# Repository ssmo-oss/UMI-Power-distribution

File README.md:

# UMI Power Distribution

Three separate boards distribute a 12 V supply to the UMI system. **D6 is the current prototype revision. It has not been physically qualified or approved for production.**

## Latest mechanical candidate — D8-2L MAIN

The owner supplied [10052938_AA-UMI POWER PCB OUTLINE V3.dxf](design/D8-2L/source/10052938_AA-UMI%20POWER%20PCB%20OUTLINE%20V3.dxf) for MAIN only on 2026-10-01. [D8-2L](design/D8-2L/README.md) and [D8-2L-FASTON](design/D8-2L-FASTON/README.md) apply the updated contour and six 3.5 mm mounting-hole centers. The FASTON assembly was corrected on 2026-10-01: the right-angle tabs now point toward board top, their through-board pins align with the two-hole footprints, and the reverse-side fuseholder envelopes align with their pad patterns. The FASTON board passes DRC with zero violations, unconnected items, and schematic-parity issues. Its [STEP assembly](design/D8-2L-FASTON/MAIN_POWER/MAIN_POWER_D8_FASTON.step) and [3D preview](design/D8-2L-FASTON/MAIN_POWER/review/MAIN_POWER_D8_FASTON_3D.png) are current. The terminal and fuseholder solids are dimension-based simplified CAD envelopes, not exact vendor models; TE lists the 63951-4 as a 6.35 mm-wide right-angle tab with 1.4 mm PCB holes and an 8.89 mm profile height ([TE product page](https://www.te.com/en/product-63951-4.html)). Raw copper is excluded and solder-mask surfaces are included in the STEP. The direct-solder variant was left untouched. TE recommends 1.57 mm PCB thickness, while the candidate remains 1.2 mm pending confirmation. D7-2L remains unchanged.

**D8 is not ready for manufacturing.** KiCad 10.0.6 DRC reports 0 violations, 0 unconnected items, and 0 schematic-parity issues for both MAIN variants. Complete electrical, thermal, and enclosure review before release. See the saved [D8 DRC report](design/D8-2L/MAIN_POWER/verification/D8_DRC_DIRECT_SOLDER.json), [board preview](design/D8-2L/MAIN_POWER/review/MAIN_POWER_D8.svg), and [visual STEP assembly](design/D8-2L/MAIN_POWER/MAIN_POWER_D8.step). The direct-solder STEP includes the board and all 10 component envelopes. The FASTON variant includes the board and all 11 component envelopes. Input leads and mating cables are omitted.

| Board | Function | PCB size / thickness | Planned assembly |
|---|---|---|---|
| MAIN_POWER | Fused 12 V distribution | 68 Ãƒâ€” 100.264 mm / 1.2 mm | User fits all 11 through-hole parts |
| POE_POWER | 12 V to nominal 53.5 V, 1.31 A switch supply | 106 Ãƒâ€” 100 mm / 1.2 mm | JLC SMT, user fits 3 through-hole parts |
| USB_POWER | Two charge-only USB-A ports, 3 A electrical design target each | 80 Ãƒâ€” 50 mm / 1.6 mm | JLC SMT, user fits 3 through-hole parts |

All boards use four copper layers, 2 oz outer / 1 oz inner. Planned batch: **10 of each board**. Enclosure ambient limit: **40 Ã‚Â°C**.

## Mechanical update required

On 2026-09-28, the project owner confirmed that the D6 board outlines were out of date. D8-2L now applies the supplied replacement outline to MAIN only. D6 manufacturing files and STEP models remain historical and on hold; POE and USB replacement mechanics are still not supplied. Do not treat D8 as released for manufacture.

## Latest MAIN option: D7-2L

[Two-layer MAIN prototype](design/D7-2L/README.md) preserves the user layout and uses 2 oz copper on each side at 1.2 mm thickness. Native ERC/DRC/parity checks pass. The four-layer D6L1 option remains preserved. Full shared-path voltage-drop/thermal qualification and mechanical confirmation remain pending. PoE and USB are unchanged. [Download D7-2L](packages/UMI_MAIN_POWER_D7_2L_PROTOTYPE.zip).

## Preserved four-layer MAIN layout: D6L1

The user rearranged MAIN components on 2026-09-29. [D6L1](design/D6L1/README.md) restores the branch connections and fills while preserving those placements and graphics. Native DRC/parity: zero violations and zero unconnected items. [Open the current MAIN project](design/D6L1/MAIN_POWER/MAIN_POWER.kicad_pro). Older MAIN Gerbers and STEP files are now stale for this layout. Manufacturing remains on hold.

## MAIN schematic redraw: D6S1

The MAIN schematic was redrawn on 2026-09-29 with explicit branch wiring. [Open the D6S1 project](design/D6S1/MAIN_POWER/MAIN_POWER.kicad_pro), [view the schematic PDF](design/D6S1/MAIN_POWER/review/MAIN_POWER_schematic.pdf), or read the [revision notes](design/D6S1/README.md). The physical MAIN PCB is unchanged from D6; PoE and USB remain D6. The outline hold still applies. For another computer or agent, read [START_HERE.md](START_HERE.md).

## Start here

- [D6 design and manufacturing overview](design/D6/README.md)
- KiCad 10 projects: [MAIN](design/D6/MAIN_POWER/MAIN_POWER.kicad_pro), [POE](design/D6/POE_POWER/POE_POWER.kicad_pro), [USB](design/D6/USB_POWER/USB_POWER.kicad_pro). Each project includes its PCB, schematic and local libraries.
- [Complete D6 prototype package](packages/UMI_THREE_BOARD_DESIGN_D6_PROTOTYPE.zip)
- [Combined component sourcing spreadsheet](design/D6/UMI_COMPONENT_SOURCING.xlsx) and [CSV](design/D6/UMI_COMPONENT_SOURCING.csv): one list for SMT, manual parts and harness parts.
- [Layout review](design/D6/LAYOUT_REVIEW.html): download/clone and open locally to view linked fabrication and assembly drawings.
- [Simplified STEP models](mechanical/D6/README.md) and [STEP ZIP](packages/UMI_D6_STEP.zip).
- [Engineering calculations and bring-up procedure](design/D6/ENGINEERING_AND_TEST_NOTES.md), [fabrication requirements](design/D6/FABRICATION_NOTES.md), [manual assembly](design/D6/MANUAL_ASSEMBLY.md).
- [Open items and project decisions](docs/PROJECT_HANDOFF.md).

## Configuration

The PoE switch and SENSING GMSL board are **alternative configurations; never connect both loads** under this power budget. No hardware interlock enforces this. The larger configuration is approximately 174 W / 14.5 A at 12 V under the documented assumptions; retain the 20 A input-path design/test margin.

MAIN J1 is the 12 V input. MAIN J2/J3/J4/J5/J6 feed Jetson/GMSL/fan/USB/POE respectively. All two-pin 12 V headers use pin 1 positive, pin 2 ground. POE J6 supplies 53.5 V: pin 1 positive, pin 2 unused, pin 3 ground. Consult the project pin schedules before making cables.

## Verification and limitations

The supplied D6 records report zero KiCad DRC/ERC violations, zero unconnected items and zero schematic-parity issues. Gerber/drill/placement checks and source hashes are included in each board's verification folder. These are file checks, not hardware measurements. [TEST_RECORD.csv](design/D6/TEST_RECORD.csv) records physical tests as unperformed.

Supplier acceptance of copper thickness, selective filled/capped vias and the PoE inductor fixture is pending. Stock observations are historical snapshots, not reservations. The output fuse is obsolete and its observed stock only supports a batch sourcing plan. No order or payment has been placed.

STEP files preserve board outlines and holes and add simplified component proxies. Component heights are estimates: do not use them for final enclosure-clearance signoff. Missing KiCad 3D bodies do not remove a component from the assembly BOM; check the SMT BOM/CPL and separately fitted parts.

## Repository contents

`design/D6/` is the editable current design and manufacturing package. `mechanical/D6/` contains six STEP models and their verification/assumptions. `packages/` contains the original current delivery ZIPs. `archive/` contains superseded snapshots, including the original revC input. `docs/historical-reviews/` preserves prior engineering reviews; they can contain findings later resolved by D6. `tools/legacy/` contains development scripts, with execution caveats in its README.

Transferred on 2026-09-28. See [transfer record](docs/TRANSFER_RECORD.md) and [SHA256 manifest](TRANSFER_SHA256SUMS.txt). No license has been selected; this import does not assign new licensing terms to project files or third-party library assets.

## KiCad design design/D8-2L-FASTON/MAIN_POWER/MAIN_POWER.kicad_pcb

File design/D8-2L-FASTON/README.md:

# D8 MAIN — FASTON 250 input alternative

This separate MAIN-board variant is based on D8-2L. It uses the owner-supplied V3 outline and keeps the fuse and connector arrangement, routing, copper zones, and output connectors. J1 is changed to two TE Connectivity 63951-4 FASTON 250 PCB tabs, each with two plated mounting holes (four holes total) on the tab axis, with both blade axes pointing toward the board's top edge in the top view. The flat solder-pad version remains in `design/D8-2L/MAIN_POWER/`.

The FASTON pair is centered on the board's 139.6 mm X centerline. Its footprint courtyard sits 2.5 mm in from the straight lower board edge.

## Input connector

- PCB terminals: TE Connectivity **63951-4**, quantity 2; FASTON 250, 6.35 × 0.8 mm tabs. Each tab uses two 1.4 mm plated holes at 5.08 mm pitch.
- Mating 10 AWG receptacle option: TE Connectivity **62998-2**, quantity 2, for 10–8 AWG wire. The mating receptacles and wires are off-board, not fitted to the PCB.
- TE lists 8.89 mm profile height from PCB for 63951-4, leaving 1.11 mm nominal margin under 10 mm. The same product page recommends 1.57 mm board thickness. This variant still uses 1.2 mm board thickness; confirm fit/retention with TE or update the stackup before ordering.
- The 10 mm clearance also needs checking with the selected female receptacles and wires installed. The TE 63951-4 summary does not state a current rating, so qualify the complete connection thermally at the intended maximum current. Terminals have no wire-insulation support; add harness strain relief.

## Files

- `MAIN_POWER/MAIN_POWER.kicad_pcb` — updated PCB; copper zones refilled.
- `MAIN_POWER/MAIN_POWER.kicad_sch` — J1 value, footprint, MPN and BOM status updated.
- `MAIN_POWER/UMI_D2.pretty/Input_FASTON_250_PAIR.kicad_mod` — pair footprint with four 1.4 mm plated holes (two per tab, 5.08 mm pitch) and top-view tab orientation shown on F.Fab.
- `MAIN_POWER/verification/D8_FASTON_DRC.json` — KiCad 10.0.6 check after V3 outline and zone refill: 0 rule violations, 0 unconnected items, and 0 schematic-parity warnings. The six DXF-derived 3.5 mm mounting holes have matching schematic records.
- `MAIN_POWER/review/MAIN_POWER_D8_FASTON.svg` — top-view preview.
- `MAIN_POWER/MAIN_POWER_D8_FASTON.step` — refreshed 2026-10-01; board, solder-mask surfaces, and all 11 modeled components (J1–J6 and F1–F5); raw tracks, pads, and zones are excluded.
- `MAIN_POWER/review/MAIN_POWER_D8_FASTON_3D.png` — 3D assembly preview showing the input blades extending toward the board top and the fuse-holder envelopes aligned over their backside pad patterns.

The STEP uses dimensioned envelope models for the TE 63951-4 terminal pair, the JST VH output headers, and the Littelfuse FLR fuse holders. They are simplified solid envelopes, not detailed vendor CAD. The FASTON pair uses a 6.35 × 0.8 mm blade, 8.89 mm profile height, four tails aligned to the four 1.4 mm holes, and a right-angle bend; the two blades point toward the board top, parallel to the fuse row. The B.Cu fuseholder envelopes are mirrored to match the pad patterns. TE recommends a 1.57 mm board; this candidate is still 1.2 mm. Confirm the terminal fit, 10 mm enclosure clearance, current capacity, and mating connector with exact vendor CAD before release. This remains a prototype layout candidate, not a manufacturing release.

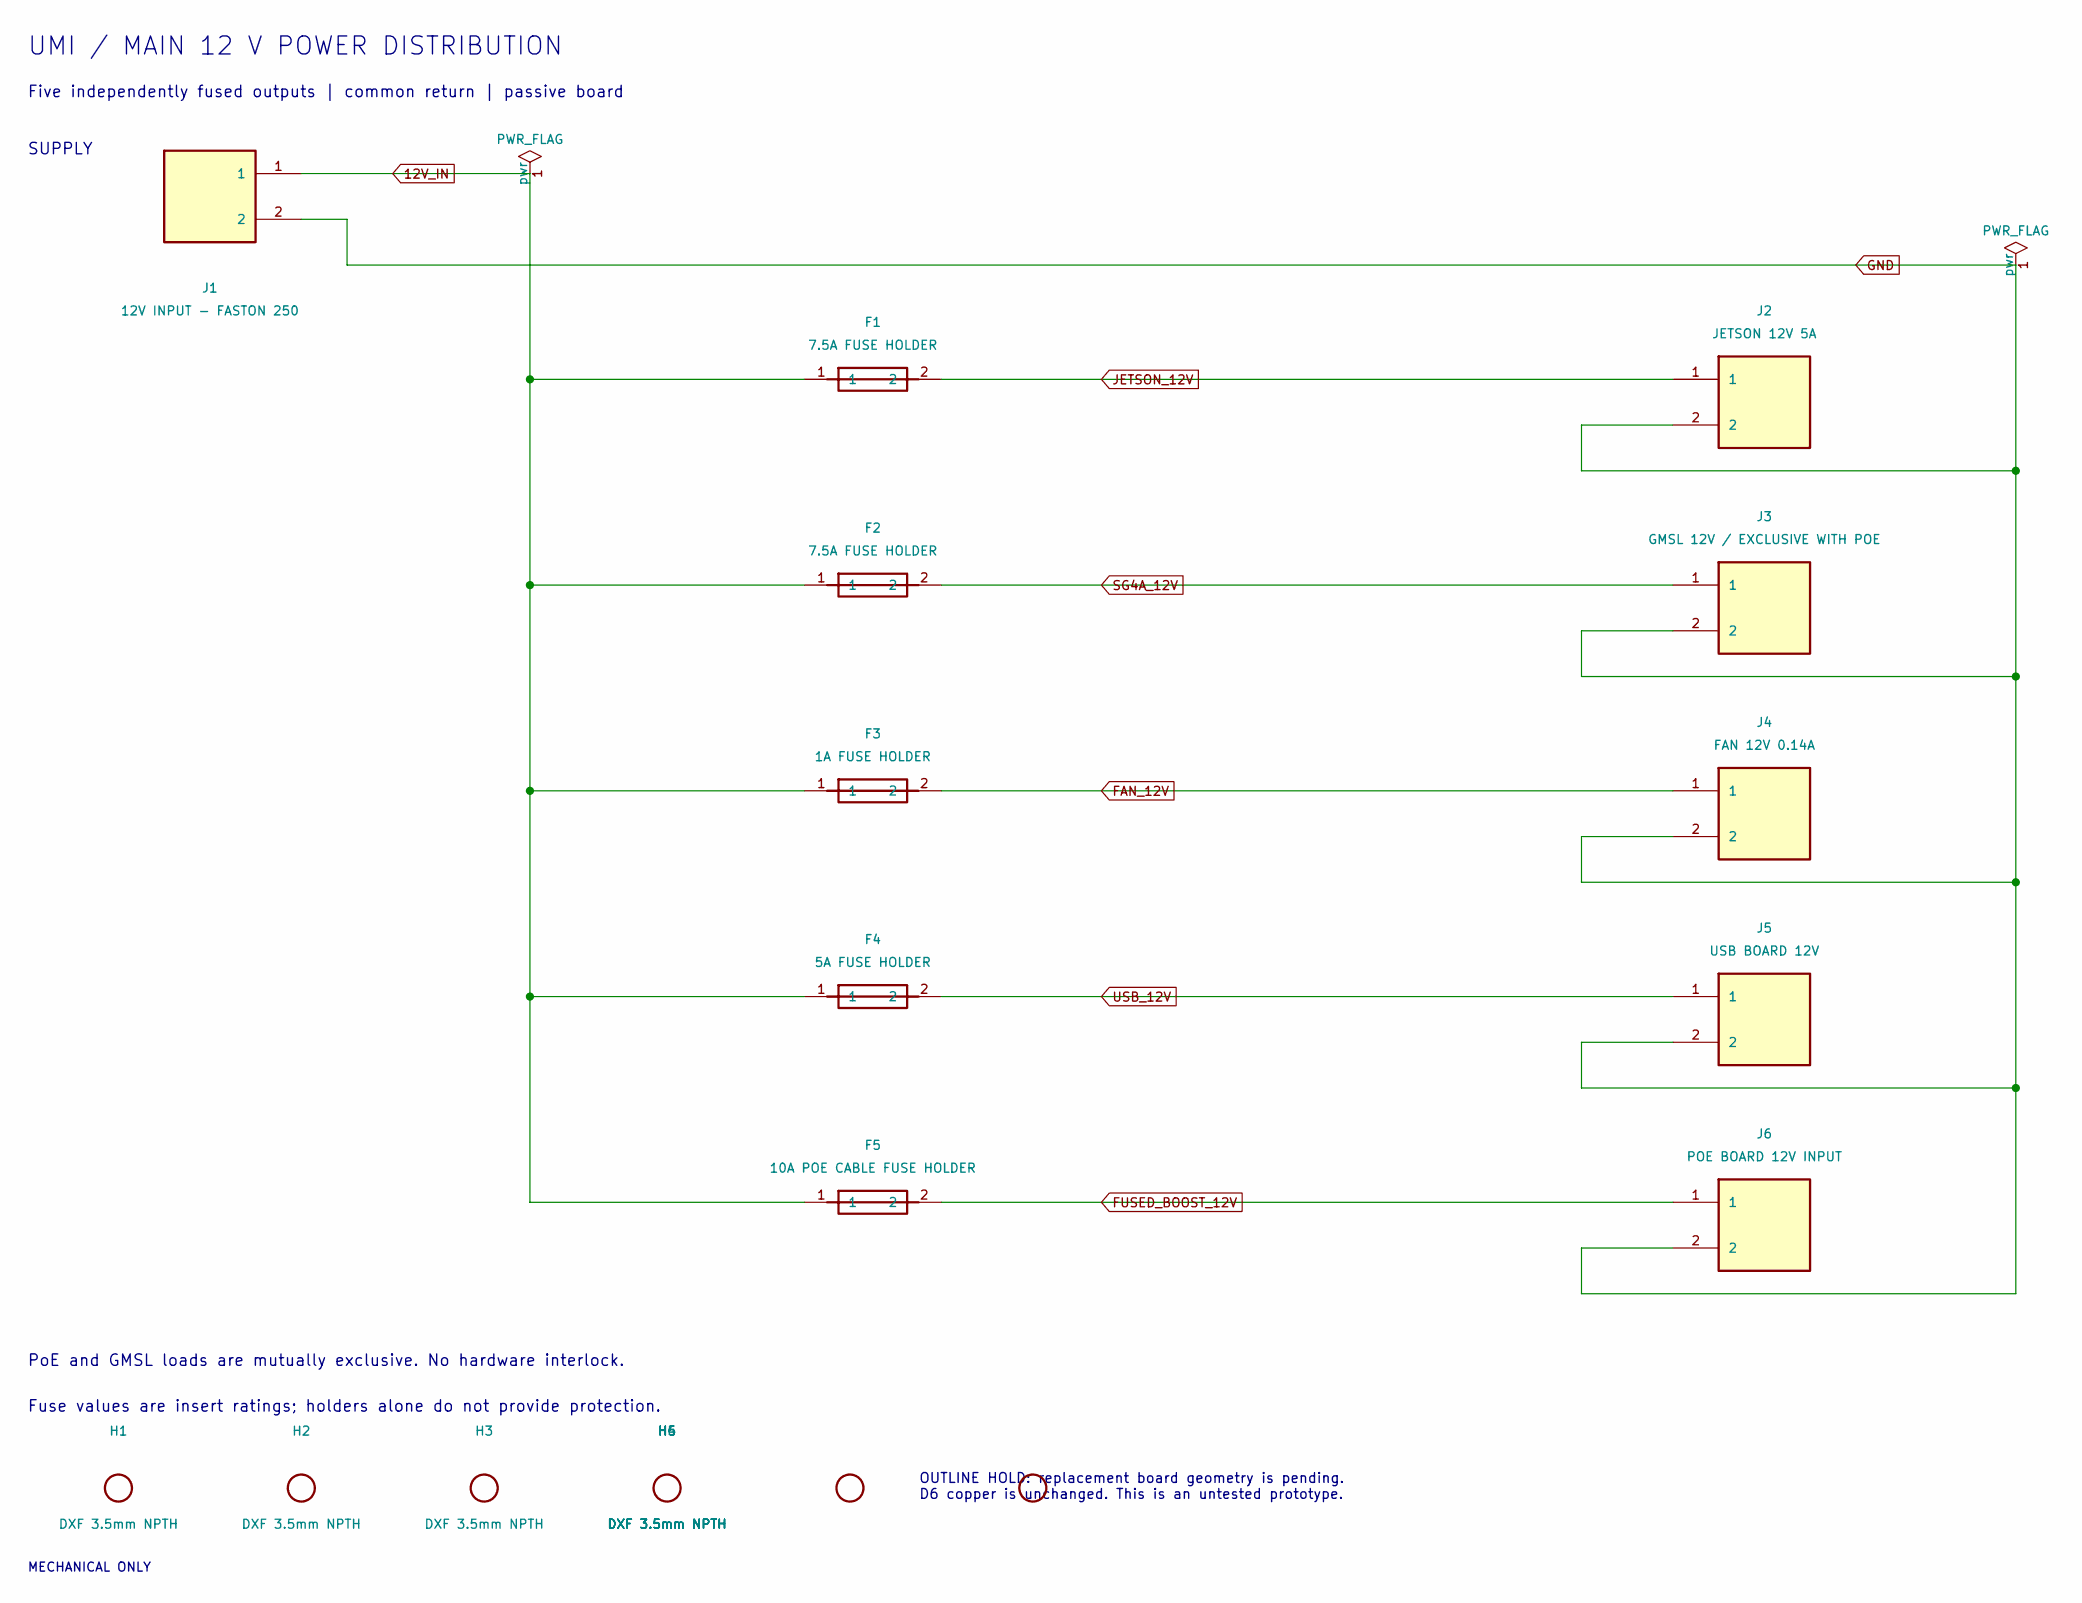
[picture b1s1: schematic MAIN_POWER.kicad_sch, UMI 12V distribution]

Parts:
F1, F2: 7.5A FUSE HOLDER; FuseHolder_Blade_ATO_Littelfuse_FLR_178.6165; MPN 178.6165.0002
F3: 1A FUSE HOLDER; FuseHolder_Blade_ATO_Littelfuse_FLR_178.6165; MPN 178.6165.0002
F4: 5A FUSE HOLDER; FuseHolder_Blade_ATO_Littelfuse_FLR_178.6165; MPN 178.6165.0002
F5: 10A POE CABLE FUSE HOLDER; FuseHolder_Blade_ATO_Littelfuse_FLR_178.6165; MPN 178.6165.0002
H1, H2, H3, H4, H5, H6: DXF 3.5mm NPTH; MountingHole_3.5mm; MPN MECHANICAL - NO PURCHASE
J1: 12V INPUT - FASTON 250; Input_FASTON_250_PAIR; MPN 63951-4 x2
J2: JETSON 12V 5A; JST_VH_B2P-VH_1x02_P3.96mm_Vertical; MPN B2P-VH(LF)(SN)
J3: GMSL 12V / EXCLUSIVE WITH POE; JST_VH_B2P-VH_1x02_P3.96mm_Vertical; MPN B2P-VH(LF)(SN)
J4: FAN 12V 0.14A; JST_VH_B2P-VH_1x02_P3.96mm_Vertical; MPN B2P-VH(LF)(SN)
J5: USB BOARD 12V; JST_VH_B2P-VH_1x02_P3.96mm_Vertical; MPN B2P-VH(LF)(SN)
J6: POE BOARD 12V INPUT; JST_VH_B2P-VH_1x02_P3.96mm_Vertical; MPN B2P-VH(LF)(SN)

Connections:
12V_IN: F1.1, F2.1, F3.1, F4.1, F5.1, J1.1
FAN_12V: F3.2, J4.1
FUSED_BOOST_12V: F5.2, J6.1
GND: J1.2, J2.2, J3.2, J4.2, J5.2, J6.2
JETSON_12V: F1.2, J2.1
SG4A_12V: F2.2, J3.1
USB_12V: F4.2, J5.1

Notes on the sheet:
UMI / MAIN 12 V POWER DISTRIBUTION
Five independently fused outputs | common return | passive board
SUPPLY
PoE and GMSL loads are mutually exclusive. No hardware interlock.
Fuse values are insert ratings; holders alone do not provide protection.
MECHANICAL ONLY
OUTLINE HOLD: replacement board geometry is pending. D6 copper is unchanged. This is an untested prototype.

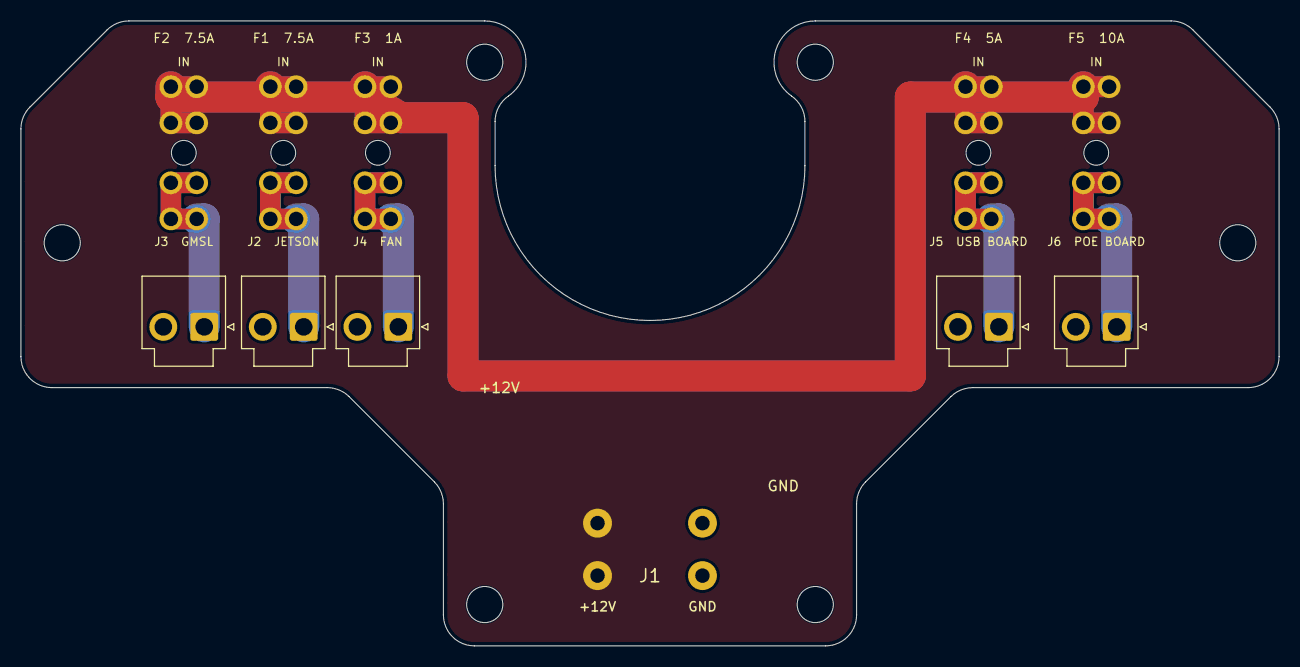
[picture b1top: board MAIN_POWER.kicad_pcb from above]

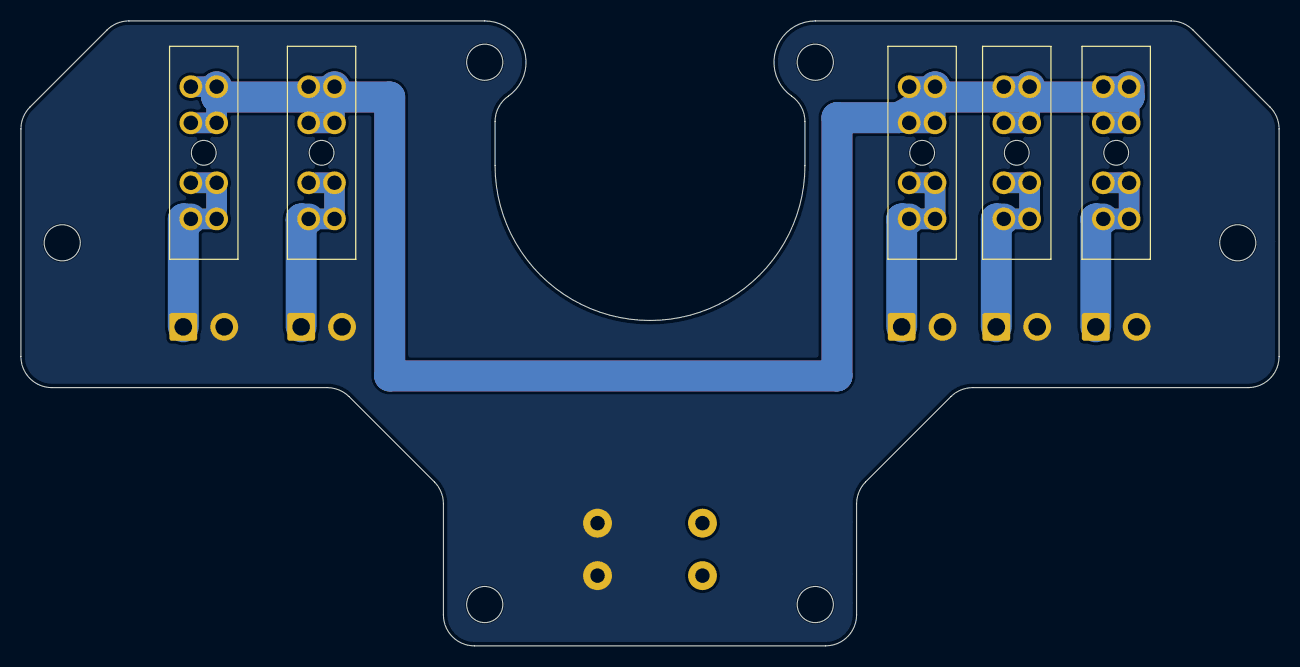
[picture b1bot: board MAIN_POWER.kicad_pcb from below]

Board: 2 copper layers, 121.8 x 60.5 mm, 17 parts (5 on the bottom side), 7 nets.

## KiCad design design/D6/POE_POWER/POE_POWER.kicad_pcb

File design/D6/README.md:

# UMI D6 — sourcing and manufacturing corrections

D6 retains the three-board architecture and resolves the known part-sourcing and file-format issues that can be handled before fabrication. **Ready for prototype manufacturing review, not physically qualified for production.**

## Completed

- Replaced the preorder snubber resistor with stocked **Yageo RC2010JK-077R5L / C4169838**. Resistance, tolerance, power rating and footprint are unchanged. Its pulse/thermal behaviour still requires the same prototype measurement as the original part.
- Found exact loose-part sources for all thirteen manual component types. The Phoenix input connector no longer needs JLC preorder. The 80 V fuse has enough observed distributor stock for twenty pieces, including ten spares. It is obsolete; this is a batch solution, not guaranteed long-term availability.
- Defined the supply route: JLC assembles SMT; the user fits separately purchased connectors, holders, inserts and harness components. All remain on **one combined spreadsheet** with purchase links and quantities. Repeated manual MPNs are bought once; later duplicate rows show zero purchase quantity.
- Corrected MAIN/POE inner-layer stackup identities, widened five POE traces from 0.15 to 0.16 mm, enlarged MAIN's small visible labels, and encoded selective via filling/capping in the PCB sources and coordinate schedules.
- Refilled and re-exported all boards. Final KiCad DRC/ERC reports pass with zero reported violations, zero unconnected items and zero schematic-parity issues. Independent Gerber/drill/placement audits and source-hash checks are included.

## Files and order scope

Open **LAYOUT_REVIEW.html** for actual fabrication previews and schematic/assembly drawings. Order ten of each:

| Board | Outline | Thickness | Copper | Assembly |
|---|---|---|---|---|
| MAIN_POWER | 68 × 100.264 mm | 1.2 mm | 4 layers, 2 oz outer / 1 oz inner | Bare board, 11 manual parts |
| POE_POWER | 106 × 100 mm | 1.2 mm | Same | 53 SMT + 3 manual parts |
| USB_POWER | 80 × 50 mm | 1.6 mm | Same | 31 SMT + 3 manual parts |

Use the per-board Gerber ZIP, SMT BOM and normalized CPL. MAIN has no SMT operation. Read FABRICATION_NOTES.md: POE/USB need selective epoxy-filled, copper-capped vias; POE's 0.635 mm vias remain ordinary. Include the POE inductor assembly fixture. The source copper stackup is explicit; do not accept a silent change to 0.5 oz inner copper.

## Electrical configuration

MAIN J1 takes 12 V. J2 supplies Jetson, J3 GMSL, J4 fan, J5 USB J1 and J6 POE J1. All 12 V two-pin headers use pin 1 positive, pin 2 ground. POE J6 is the 53.5 V output: pin 1 positive, pin 2 empty, pin 3 ground.

Use **PoE or GMSL, never both**. There is no electronic interlock. The larger configuration is approximately **174 W / 14.5 A at 12 V**, using the documented allowances and assumed converter efficiency; retain 20 A input-path design/test margin. MAIN retains F1 Jetson 7.5 A, F2 GMSL 7.5 A, F3 fan 1 A, F4 USB 5 A and F5 PoE feed 10 A. POE retains F6 3 A / 80 V. F5 protects the interboard cable at its source. Jetson's 7.5 A is provisional protection, not expected draw; verify startup, temperature and wire protection before changing it.

## Remaining external steps

1. **Manufacturer acceptance and purchasing:** the exact copper/thickness/selective-fill combination and inductor fixture need an accepted quote. QUOTE_REQUEST.md is prepared but unsent. Approve supplier placement/polarity previews and final attrition quantities. C1 requires fourteen pieces including the reported four-piece attrition, against fifteen observed; L1 requires ten against seventeen observed. Inventory is not reserved. Other SMT allowances in the spreadsheet are conservative planning quantities where exact order-page arithmetic was unavailable.
2. **Physical prototype tests:** no assembled hardware was available to test. Thermal rise at 40 °C, stability, snubber pulses, eFuse fault transients, USB load steps and real-device compatibility cannot be established from DRC. TEST_RECORD.csv gives the pending measurements; ENGINEERING_AND_TEST_NOTES.md gives the procedure. All physical results are explicitly unperformed.
3. **Installation details:** final cable lengths, device-end plugs, weakest wire/pigtail ratings, input cable protection and the exact USB-powered device model remain to be confirmed before system integration. The interim interboard harness basis is AWG16, at most 1 m one-way; this is a documented assumption, not a measured installation.

No supplier message, order, reservation, payment or external design upload has been made. D5 is preserved. SHA256SUMS.txt identifies this package.

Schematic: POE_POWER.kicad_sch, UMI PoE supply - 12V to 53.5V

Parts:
C1: 470pF 100V; C_0805_2012Metric_R90; MPN C0805C471J1GACTU
C2, C3, C4, C5, C6, C7, C8: 4.7uF 80V; C_1210_3225Metric_R90; MPN GRM32ER71K475KE14L
C9: 100nF 25V; C_0603_1608Metric_R180; MPN GRM188R71E104KA01D
C10: 100pF 50V; C_0603_1608Metric; MPN GRM1885C1H101JA01D
C11: 1uF 16V; C_0603_1608Metric_R180; MPN GCM188R71C105KA64D
C13: 100pF 50V; C_0603_1608Metric_R90; MPN GRM1885C1H101JA01D
C14: 47nF 50V; C_0603_1608Metric_R270; MPN CC0603KRX7R9BB473
C15: 470nF 100V; C_0805_2012Metric_R90; MPN GRM21BR72A474KA73L
C16: 100nF 25V; C_0603_1608Metric_R90; MPN GRM188R71E104KA01D
C17: 1500pF 50V; C_0603_1608Metric_R90; MPN GRM1885C1H152JA01D
C18: 15nF 50V; C_0603_1608Metric; MPN CC0603KRX7R9BB153
C19, C20: 47uF 80V; Panasonic_FK_G_10x10.2_R90; MPN EEE-FK1K470P
C21: 1uF 50V X7R; C_0805_2012Metric; MPN GRM21BR71H105KA12L
C22: 100nF 50V; C_0603_1608Metric; MPN GRM188R71H104KA93D
C23: 6.8nF 50V C0G; C_0603_1608Metric; MPN GRM1885C1H682JA01D
D2: MBR1H100SFT3G; D_SOD-123F; MPN NRVB1H100SFT3G
D3: SMBJ15A; D_SMB; MPN SMBJ15A
D4: SS10P4-M3/86A; TO-277A; MPN SS10P4-M3/86A
F6: 3A 80V BOOST OUTPUT FUSE HOLDER; FuseHolder_Blade_ATO_Littelfuse_FLR_178.6165; MPN 178.6165.0002
H1, H2, H3, H4: MountingHole_3.2mm_M3; MPN MECHANICAL
J1: 12V FROM MAIN; JST_VH_B2P-VH_1x02_P3.96mm_Vertical; MPN B2P-VH(LF)(SN)
J6: SWITCH 53.5V 1.31A; JST_VH_B3P-VH_1x03_P3.96mm_Vertical; MPN B3P-VH(LF)(SN)
L1: 10uH; Coilcraft_SER2915H; MPN SER2915H-103KL
L2: 1uH; L_Coilcraft_XAL4020-XXX; MPN XAL4020-102MEC
Q1, Q2, Q3: BSC040N08NS5; BSC072N08NS5_TDSON_8_R270; MPN BSC040N08NS5
R1: 7.5; R_2010_5025Metric_R270; MPN RC2010JK-077R5L
R2: 4m 1%; EverOhms_MA2512_2to5mOhm_R270; MPN MA251230FR004MZ
R3, R4: 100; R_0603_1608Metric_R90; MPN ESR03EZPJ101
R5, R8: 0; R_0603_1608Metric_R90; MPN ERJ-3GEY0R00V
R10: 49.9k; R_0603_1608Metric_R90; MPN CRCW060349K9FKEA
R11: 3.3 1%; R_0603_1608Metric_R90; MPN RC0603FR-073R3L
R12: 0; R_0603_1608Metric_R270; MPN ERJ-3GEY0R00V
R13: 8.45k; R_0603_1608Metric_R270; MPN RC0603FR-078K45L
R14: 30k; R_0603_1608Metric_R90; MPN CRCW060330K0JNEA
R16: 40.2k; R_0603_1608Metric_R270; MPN CRCW060340K2FKEA
R17: 20.5k; R_0603_1608Metric_R270; MPN CRCW060320K5FKEA
R18: 1.96k 0.1%; R_0603_1608Metric_R180; MPN RT0603BRD071K96L
R19: 84.5k 0.1%; R_0603_1608Metric; MPN ERA-3AEB8452V
R20: 953 0.1%; R_0603_1608Metric; MPN RT0603BRD07953RL
R21: 0; R_0603_1608Metric; MPN ERJ-3GEY0R00V
R22: 100k 0.1%; R_0603_1608Metric; MPN RT0603BRD07100KL
R23: 13.7k 0.1%; R_0603_1608Metric; MPN RT0603BRD0713K7L
R24: 182 0.1%; R_0603_1608Metric; MPN RT0603BRD07182RL
R25: 511 0.1%; R_0603_1608Metric; MPN RT0603BRD07511RL
U1: LM5122MHX/NOPB; HTSSOP-20-1EP_4.4x6.5mm_P0.65mm_EP3.4x6.5mm_Mask2.4x3.7mm_R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; MPN LM5122MHX/NOPB
U2: TPS259824ONRGER; TI_RGE0024M_TPS25982; MPN TPS259824ONRGER

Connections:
12V_IN: C21.1, C22.1, D3.1 (K), J1.1 (+12V), R22.1, U2.1 (IN), U2.2 (IN), U2.3 (IN), U2.16 (IN), U2.25 (IN)
53V5_RAW: C20.1 (+), F6.1, L2.2, R20.2
BOOST_IN: C2.1, C3.1, C4.1, C19.1 (+), D4.3 (K), R2.1, R3.2, R10.2, R11.2, U2.17 (OUT), U2.18 (OUT), U2.19 (OUT), U2.20 (OUT), U2.21 (OUT), U2.22 (OUT), U2.23 (OUT), U2.24 (OUT)
BOOST_OUT: C5.1, C6.1, C7.1, C8.1, L2.1, Q1.5 (D), Q1.6 (D), Q1.7 (D), Q1.8 (D), R1.2
BST: C9.2, D2.1 (K), U1.20 (BST)
COMP: C17.1, C18.1, U1.11 (COMP)
COMP_RC: C18.2, R17.2
CSN: C10.1, R4.1, U1.3 (CSN)
CSP: C10.2, R3.1, U1.4 (CSP)
EFUSE_DVDT: C23.1, U2.15 (DVDT)
EFUSE_EN: R22.2, R23.1, U2.6 (EN_UVLO)
EFUSE_ILIM: R24.1, U2.8 (ILIM)
EFUSE_IMON: R25.1, U2.9 (IMON)
FB: C17.2, R17.1, R18.2, R19.1, U1.10 (FB)
FB_HIGH: R19.2, R20.1
GATE2: Q2.4 (G), R5.1
GATE3: Q3.4 (G), R21.1
GND: C2.2, C3.2, C4.2, C5.2, C6.2, C7.2, C8.2, C11.1, C13.2, C14.2, C15.2, C16.2, C19.2 (-), C20.2 (-), C21.2, C22.2, C23.2, D3.2 (A), D4.1 (A1), D4.2 (A2), J1.2 (RETURN), J6.3 (RETURN), Q2.1 (S), Q2.2 (S), Q2.3 (S), Q3.1 (S), Q3.2 (S), Q3.3 (S), R8.1, R13.1, R14.1, R16.1, R18.1, R23.2, R24.2, R25.2, U1.9 (AGND), U1.15 (PGND), U1.21 (EP), U2.4 (GND), U2.5 (GND), U2.10 (RETRY_DLY), U2.12 (LDSTRT), U2.14 (GND), U2.26 (GND)
HO: Q1.4 (G), U1.19 (HO)
IC_VIN: C15.1, R11.1, U1.5 (VIN)
LO: R5.2, R21.2, U1.16 (LO)
MODE: R12.1, U1.13 (MODE)
OPT: R8.2, U1.2 (OPT)
RES: C14.1, U1.14 (RES)
RT: R16.2, U1.8 (RT)
SENSE_LOW: L1.1 (IN), R2.2, R4.2
SLOPE: R14.2, U1.12 (SLOPE)
SNUB: C1.1, R1.1
SS: C16.1, U1.7 (SS)
SW: C1.2, C9.1, L1.2 (OUT), Q1.1 (S), Q1.2 (S), Q1.3 (S), Q2.5 (D), Q2.6 (D), Q2.7 (D), Q2.8 (D), Q3.5 (D), Q3.6 (D), Q3.7 (D), Q3.8 (D), U1.18 (SW)
SWITCH_53V5: F6.2, J6.1 (+53V5)
UVLO: C13.1, R10.1, R13.2, U1.6 (UVLO), U2.13 (PG)
VCC: C11.2, D2.2 (A), R12.2, U1.17 (VCC)

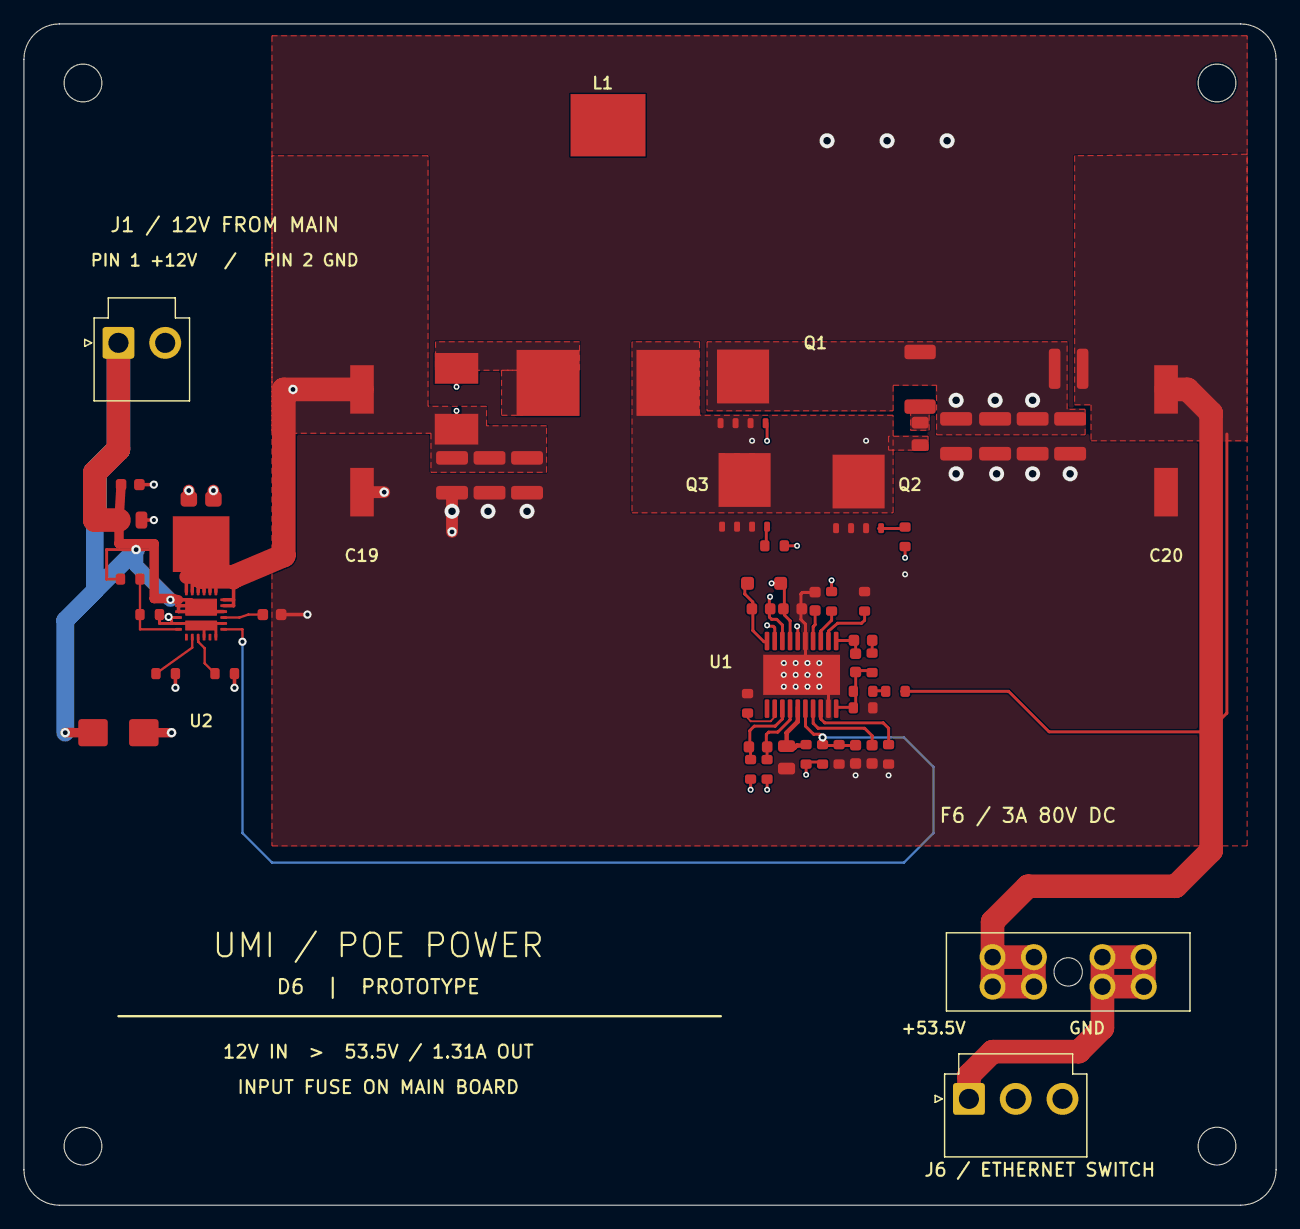
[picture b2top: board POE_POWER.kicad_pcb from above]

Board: 4 copper layers, 106.0 x 100.0 mm, 60 parts (0 on the bottom side), 33 nets.

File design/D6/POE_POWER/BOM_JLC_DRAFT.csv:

Comment,Designator,Footprint,LCSC Part #,Manufacturer,MPN
LM5122MHX/NOPB,U1,Package_SO:HTSSOP-20-1EP_4.4x6.5mm_P0.65mm_EP3.4x6.5mm_Mask2.4x3.7mm,C77241,Texas Instruments,LM5122MHX/NOPB
10uH,L1,UMI_D2:Coilcraft_SER2915H,C19276042,Coilcraft,SER2915H-103KL
1uH,L2,Inductor_SMD:L_Coilcraft_XAL4020-XXX,C4555951,Coilcraft,XAL4020-102MEC
BSC040N08NS5,"Q1,Q2,Q3",UMI_D2:BSC072N08NS5_TDSON_8,C534333,Infineon Technologies,BSC040N08NS5
470pF 100V,C1,Capacitor_SMD:C_0805_2012Metric,C23481145,KEMET,C0805C471J1GACTU
4.7uF 80V,"C2,C3,C4,C5,C6,C7,C8",Capacitor_SMD:C_1210_3225Metric,C711060,Murata,GRM32ER71K475KE14L
100nF 25V,C9,Capacitor_SMD:C_0603_1608Metric,C77050,Murata,GRM188R71E104KA01D
100pF 50V,C10,Capacitor_SMD:C_0603_1608Metric,C71664,Murata,GRM1885C1H101JA01D
1uF 16V,C11,Capacitor_SMD:C_0603_1608Metric,C161212,Murata,GCM188R71C105KA64D
100pF 50V,C13,Capacitor_SMD:C_0603_1608Metric,C71664,Murata,GRM1885C1H101JA01D
47nF 50V,C14,Capacitor_SMD:C_0603_1608Metric,C107093,Yageo,CC0603KRX7R9BB473
470nF 100V,C15,Capacitor_SMD:C_0805_2012Metric,C97926,Murata,GRM21BR72A474KA73L
100nF 25V,C16,Capacitor_SMD:C_0603_1608Metric,C77050,Murata,GRM188R71E104KA01D
1500pF 50V,C17,Capacitor_SMD:C_0603_1608Metric,C162204,Murata,GRM1885C1H152JA01D
15nF 50V,C18,Capacitor_SMD:C_0603_1608Metric,C107076,Yageo,CC0603KRX7R9BB153
47uF 80V,"C19,C20",UMI_D2:Panasonic_FK_G_10x10.2,C178556,Panasonic,EEE-FK1K470P
7.5,R1,Resistor_SMD:R_2010_5025Metric,C4169838,Yageo,RC2010JK-077R5L
4m 1%,R2,UMI_D2:EverOhms_MA2512_2to5mOhm,C252682,Ever Ohms Tech,MA251230FR004MZ
100,"R3,R4",Resistor_SMD:R_0603_1608Metric,C253328,ROHM,ESR03EZPJ101
0,"R5,R8",Resistor_SMD:R_0603_1608Metric,C122704,Panasonic,ERJ-3GEY0R00V
0,R21,Resistor_SMD:R_0603_1608Metric,C122704,Panasonic,ERJ-3GEY0R00V
49.9k,R10,Resistor_SMD:R_0603_1608Metric,C844789,Vishay,CRCW060349K9FKEA
3.3 1%,R11,Resistor_SMD:R_0603_1608Metric,C137725,Yageo,RC0603FR-073R3L
0,R12,Resistor_SMD:R_0603_1608Metric,C122704,Panasonic,ERJ-3GEY0R00V
8.45k,R13,Resistor_SMD:R_0603_1608Metric,C163417,Yageo,RC0603FR-078K45L
30k,R14,Resistor_SMD:R_0603_1608Metric,C2076641,Vishay,CRCW060330K0JNEA
40.2k,R16,Resistor_SMD:R_0603_1608Metric,C844784,Vishay,CRCW060340K2FKEA
20.5k,R17,Resistor_SMD:R_0603_1608Metric,C844143,Vishay,CRCW060320K5FKEA
1.96k 0.1%,R18,Resistor_SMD:R_0603_1608Metric,C861213,Yageo,RT0603BRD071K96L
84.5k 0.1%,R19,Resistor_SMD:R_0603_1608Metric,C4295220,Panasonic,ERA-3AEB8452V
953 0.1%,R20,Resistor_SMD:R_0603_1608Metric,C861604,Yageo,RT0603BRD07953RL
MBR1H100SFT3G,D2,Diode_SMD:D_SOD-123F,C604266,onsemi,NRVB1H100SFT3G
TPS259824ONRGER,U2,UMI_D2:TI_RGE0024M_TPS25982,C2155766,Texas Instruments,TPS259824ONRGER
100k 0.1%,R22,Resistor_SMD:R_0603_1608Metric,C122538,Yageo,RT0603BRD07100KL
13.7k 0.1%,R23,Resistor_SMD:R_0603_1608Metric,C861119,Yageo,RT0603BRD0713K7L
182 0.1%,R24,Resistor_SMD:R_0603_1608Metric,C705731,Yageo,RT0603BRD07182RL
511 0.1%,R25,Resistor_SMD:R_0603_1608Metric,C861455,Yageo,RT0603BRD07511RL
1uF 50V X7R,C21,Capacitor_SMD:C_0805_2012Metric,C77083,Murata,GRM21BR71H105KA12L
100nF 50V,C22,Capacitor_SMD:C_0603_1608Metric,C77055,Murata,GRM188R71H104KA93D
6.8nF 50V C0G,C23,Capacitor_SMD:C_0603_1608Metric,C162241,Murata,GRM1885C1H682JA01D
SMBJ15A,D3,Diode_SMD:D_SMB,C83846,Littelfuse,SMBJ15A
SS10P4-M3/86A,D4,Package_TO_SOT_SMD:TO-277A,C968538,Vishay,SS10P4-M3/86A

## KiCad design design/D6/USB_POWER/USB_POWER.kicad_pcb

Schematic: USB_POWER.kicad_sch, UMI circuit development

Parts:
C1: 10uF 50V X7R; C_1210_3225Metric_R180; MPN CNA6P1X7R1H106KT000A
C2: 10uF 50V X7R; C_1210_3225Metric; MPN CNA6P1X7R1H106KT000A
C3: 47uF 10V X7R; C_1210_3225Metric_R180; MPN GRM32ER71A476ME15L
C4, C5, C8, C11: 100nF 25V; C_0603_1608Metric; MPN GRM188R71E104KA01D
C6, C7: 22uF 10V; C_1206_3216Metric; MPN GRM31CR71A226KE15L
C9, C10, C13, C14: 47uF 10V X7R; C_1210_3225Metric; MPN GRM32ER71A476ME15L
C12: 47uF 25V bulk; CP_Elec_6.3x5.8; MPN EEE-FK1E470P
D1: 12V gate clamp; D_SOD-123; MPN BZT52C12-7-F
H1, H2, H3, H4: M3 MOUNT; MountingHole_3.2mm_M3; MPN MECHANICAL - NO PURCHASE
J1: 12V INPUT; JST_VH_B2P-VH_1x02_P3.96mm_Vertical; MPN B2P-VH(LF)(SN)
J2, J3: USB-A 3A; USB_A_Wurth_614004190021; MPN 614004190021
Q1: AO4407A; SOIC-8_3.9x4.9mm_P1.27mm; MPN AO4407A
R1: 24.9k 0.1%; R_0603_1608Metric_R180; MPN RT0603BRD0724K9L
R2, R3: 32.4k 0.1%; R_0603_1608Metric; MPN RT0603BRD0732K4L
R4, R5, R6, R9: 100k; R_0603_1608Metric; MPN RC0603FR-07100KL
R7: 102k 0.1%; R_0603_1608Metric; MPN RT0603BRD07102KL
R8: 15.8k 1%; R_0603_1608Metric; MPN ERJ-3EKF1582V
U1: TPSM63610RDFR; TI_RDF0022A_TPSM63610; MPN TPSM63610RDFR
U2, U3: TPS2557DRB; VSON-8-1EP_3x3mm_P0.65mm_EP1.65x2.4mm; MPN TPS2557DRBR
U4: TPS2513ADBVR; SOT-23-6; MPN TPS2513ADBVR
U5, U6: USBLC6-2SC6; SOT-23-6; MPN USBLC6-2SC6

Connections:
5V_BUS: C3.1, C4.1, C5.1, C8.1, C9.1, C10.1, C11.1, C13.1, C14.1, R4.1, R5.1, R7.1, R9.1, U1.5 (VLDOIN), U1.9 (VOUT1), U1.10 (VOUT2), U2.2 (IN), U2.3 (IN), U2.4 (EN), U3.2 (IN), U3.3 (IN), U3.4 (EN), U4.5 (IN)
12V_IN: J1.1 (VIN), Q1.5 (D), Q1.6 (D), Q1.7 (D), Q1.8 (D)
12V_PROTECTED: C1.1, C2.1, C12.1 (+), D1.1 (K), Q1.1 (S), Q1.2 (S), Q1.3 (S), U1.1 (VIN1), U1.17 (EN), U1.18 (VIN2)
BOOT: U1.2 (RBOOT), U1.3 (CBOOT)
DM1: J2.2 (D-), U4.6 (DM1), U5.1 (IO1), U5.6 (IO1)
DM2: J3.2 (D-), U4.4 (DM2), U6.1 (IO1), U6.6 (IO1)
DP1: J2.3 (D+), U4.1 (DP1), U5.3 (IO2), U5.4 (IO2)
DP2: J3.3 (D+), U4.3 (DP2), U6.3 (IO2), U6.4 (IO2)
FAULT1: R4.2, U2.8 (FAULT)
FAULT2: R5.2, U3.8 (FAULT)
FB: R1.1, R7.2, U1.8 (FB)
GND: C1.2, C2.2, C3.2, C4.2, C5.2, C6.2, C7.2, C8.2, C9.2, C10.2, C11.2, C12.2 (-), C13.2, C14.2, J1.2 (GND), J2.4 (GND), J2.SH (SHIELD), J3.4 (GND), J3.SH (SHIELD), R1.2, R2.2, R3.2, R6.2, R8.2, U1.7 (AGND), U1.11 (AGND), U1.14 (SPSP), U1.19 (PGND), U1.20 (PGND), U1.21 (AGND), U1.22 (AGND), U2.1 (GND), U2.9 (EP), U3.1 (GND), U3.9 (EP), U4.2 (GND), U5.2 (GND), U6.2 (GND)
ILIM1: R2.1, U2.5 (ILIM)
ILIM2: R3.1, U3.5 (ILIM)
PG: R9.2, U1.13 (PG)
RP_GATE: D1.2 (A), Q1.4 (G), R6.1
RT: R8.1, U1.12 (RT)
VBUS1: C6.1, J2.1 (VBUS), U2.6 (OUT), U2.7 (OUT), U5.5 (VBUS)
VBUS2: C7.1, J3.1 (VBUS), U3.6 (OUT), U3.7 (OUT), U6.5 (VBUS)
VCC: U1.6 (VCC), U1.15 (SYNC_MODE)

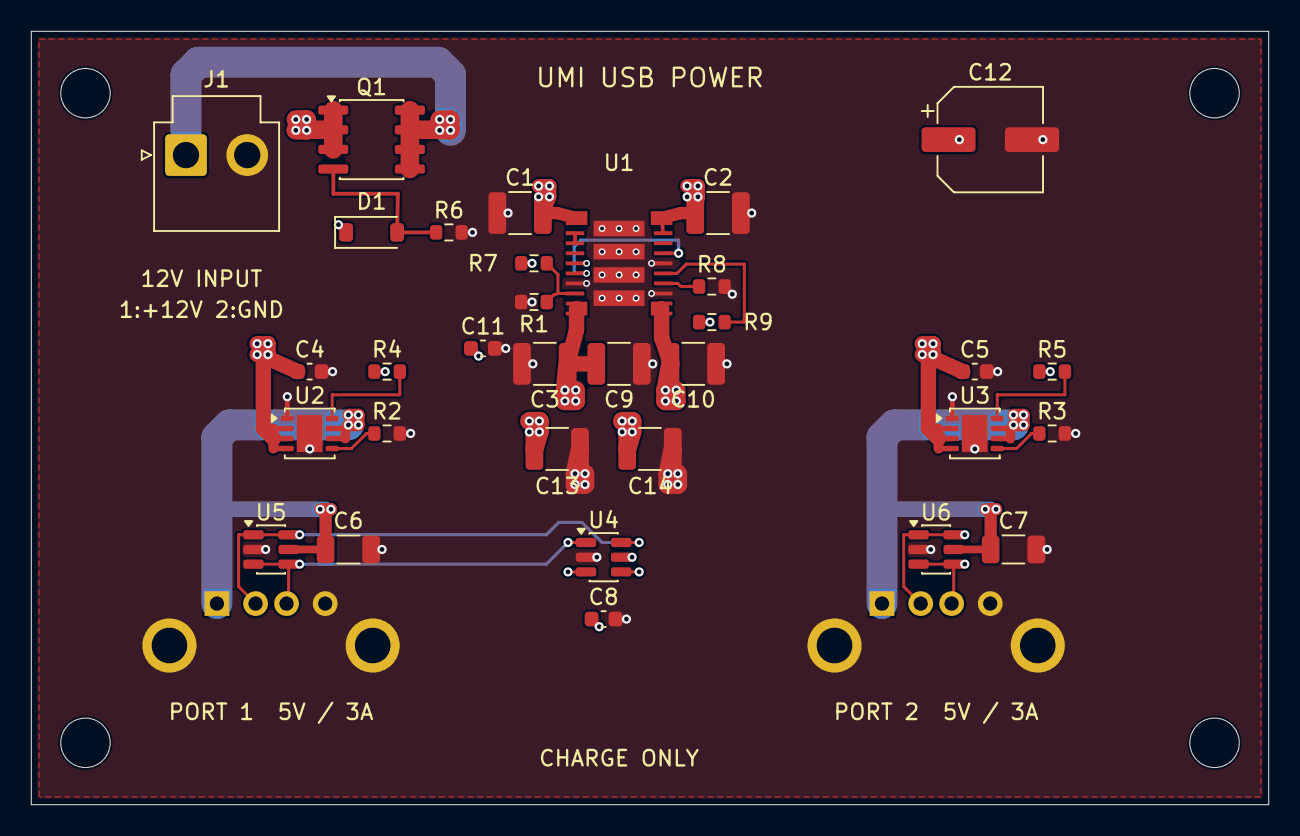
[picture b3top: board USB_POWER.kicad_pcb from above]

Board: 4 copper layers, 80.0 x 50.0 mm, 38 parts (0 on the bottom side), 20 nets.

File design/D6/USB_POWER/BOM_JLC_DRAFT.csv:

Comment,Designator,Footprint,LCSC Part #,Manufacturer,MPN
AO4407A,Q1,Package_SO:SOIC-8_3.9x4.9mm_P1.27mm,C16072,Alpha & Omega Semiconductor,AO4407A
100k,"R6,R9,R4,R5",Resistor_SMD:R_0603_1608Metric,C14675,Yageo,RC0603FR-07100KL
12V gate clamp,D1,Diode_SMD:D_SOD-123,C124196,Diodes Incorporated,BZT52C12-7-F
TPSM63610RDFR,U1,UMI_D2:TI_RDF0022A_TPSM63610,C7125816,Texas Instruments,TPSM63610RDFR
10uF 50V X7R,C1,Capacitor_SMD:C_1210_3225Metric,C694544,TDK,CNA6P1X7R1H106KT000A
10uF 50V X7R,C2,Capacitor_SMD:C_1210_3225Metric,C694544,TDK,CNA6P1X7R1H106KT000A
47uF 10V X7R,C3,Capacitor_SMD:C_1210_3225Metric,C415541,Murata,GRM32ER71A476ME15L
47uF 10V X7R,"C9,C10,C13,C14",Capacitor_SMD:C_1210_3225Metric,C415541,Murata,GRM32ER71A476ME15L
24.9k 0.1%,R1,Resistor_SMD:R_0603_1608Metric,C136967,Yageo,RT0603BRD0724K9L
102k 0.1%,R7,Resistor_SMD:R_0603_1608Metric,C861068,Yageo,RT0603BRD07102KL
15.8k 1%,R8,Resistor_SMD:R_0603_1608Metric,C403003,Panasonic,ERJ-3EKF1582V
100nF 25V,"C11,C4,C5,C8",Capacitor_SMD:C_0603_1608Metric,C77050,Murata,GRM188R71E104KA01D
47uF 25V bulk,C12,Capacitor_SMD:CP_Elec_6.3x5.8,C178545,Panasonic,EEE-FK1E470P
TPS2557DRB,"U2,U3",Package_SON:VSON-8-1EP_3x3mm_P0.65mm_EP1.65x2.4mm,C130056,Texas Instruments,TPS2557DRBR
32.4k 0.1%,"R2,R3",Resistor_SMD:R_0603_1608Metric,C861323,Yageo,RT0603BRD0732K4L
22uF 10V,"C6,C7",Capacitor_SMD:C_1206_3216Metric,C91604,Murata,GRM31CR71A226KE15L
USBLC6-2SC6,"U5,U6",Package_TO_SOT_SMD:SOT-23-6,C7519,STMicroelectronics,USBLC6-2SC6
TPS2513ADBVR,U4,Package_TO_SOT_SMD:SOT-23-6,C473910,Texas Instruments,TPS2513ADBVR
